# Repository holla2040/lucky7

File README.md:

Lucky7
======

7-Output Power Control Arduino Shield with sensor inputs and IR sensor<br><br>
Features<br>
1. 7 high-current (12A max) P-channel high-side MOSFETs with gate drivers. These switches have 30mOhm Rds when on. Each output has an LED indicator. 6 of the outputs are PWM controllable.<br>
2. The shield can operate up to 30VDC and supplies this voltage to the Arduino board.<br>
3. Two additional LEDs are connected to Arduino pin 8 and 13.<br>
4. 3 analog inputs: 2 for photocells, 1 for user button.<br>
5. 1 IR sensor input, such as TSOP38238.<br>
6. Input voltage sense to Arduino analog input A0.<br>
7. ATO fuse holder for wire protection in case of shorts to ground.<br>
8. Hardware design and firmware are released CC-BY-SA<br>
<br>
Fully populated and tested board is available for $20 + shipping.  Contact holla@montrosemakerspace.com for more information.
<br>
<br>
Only 10 available, order now!

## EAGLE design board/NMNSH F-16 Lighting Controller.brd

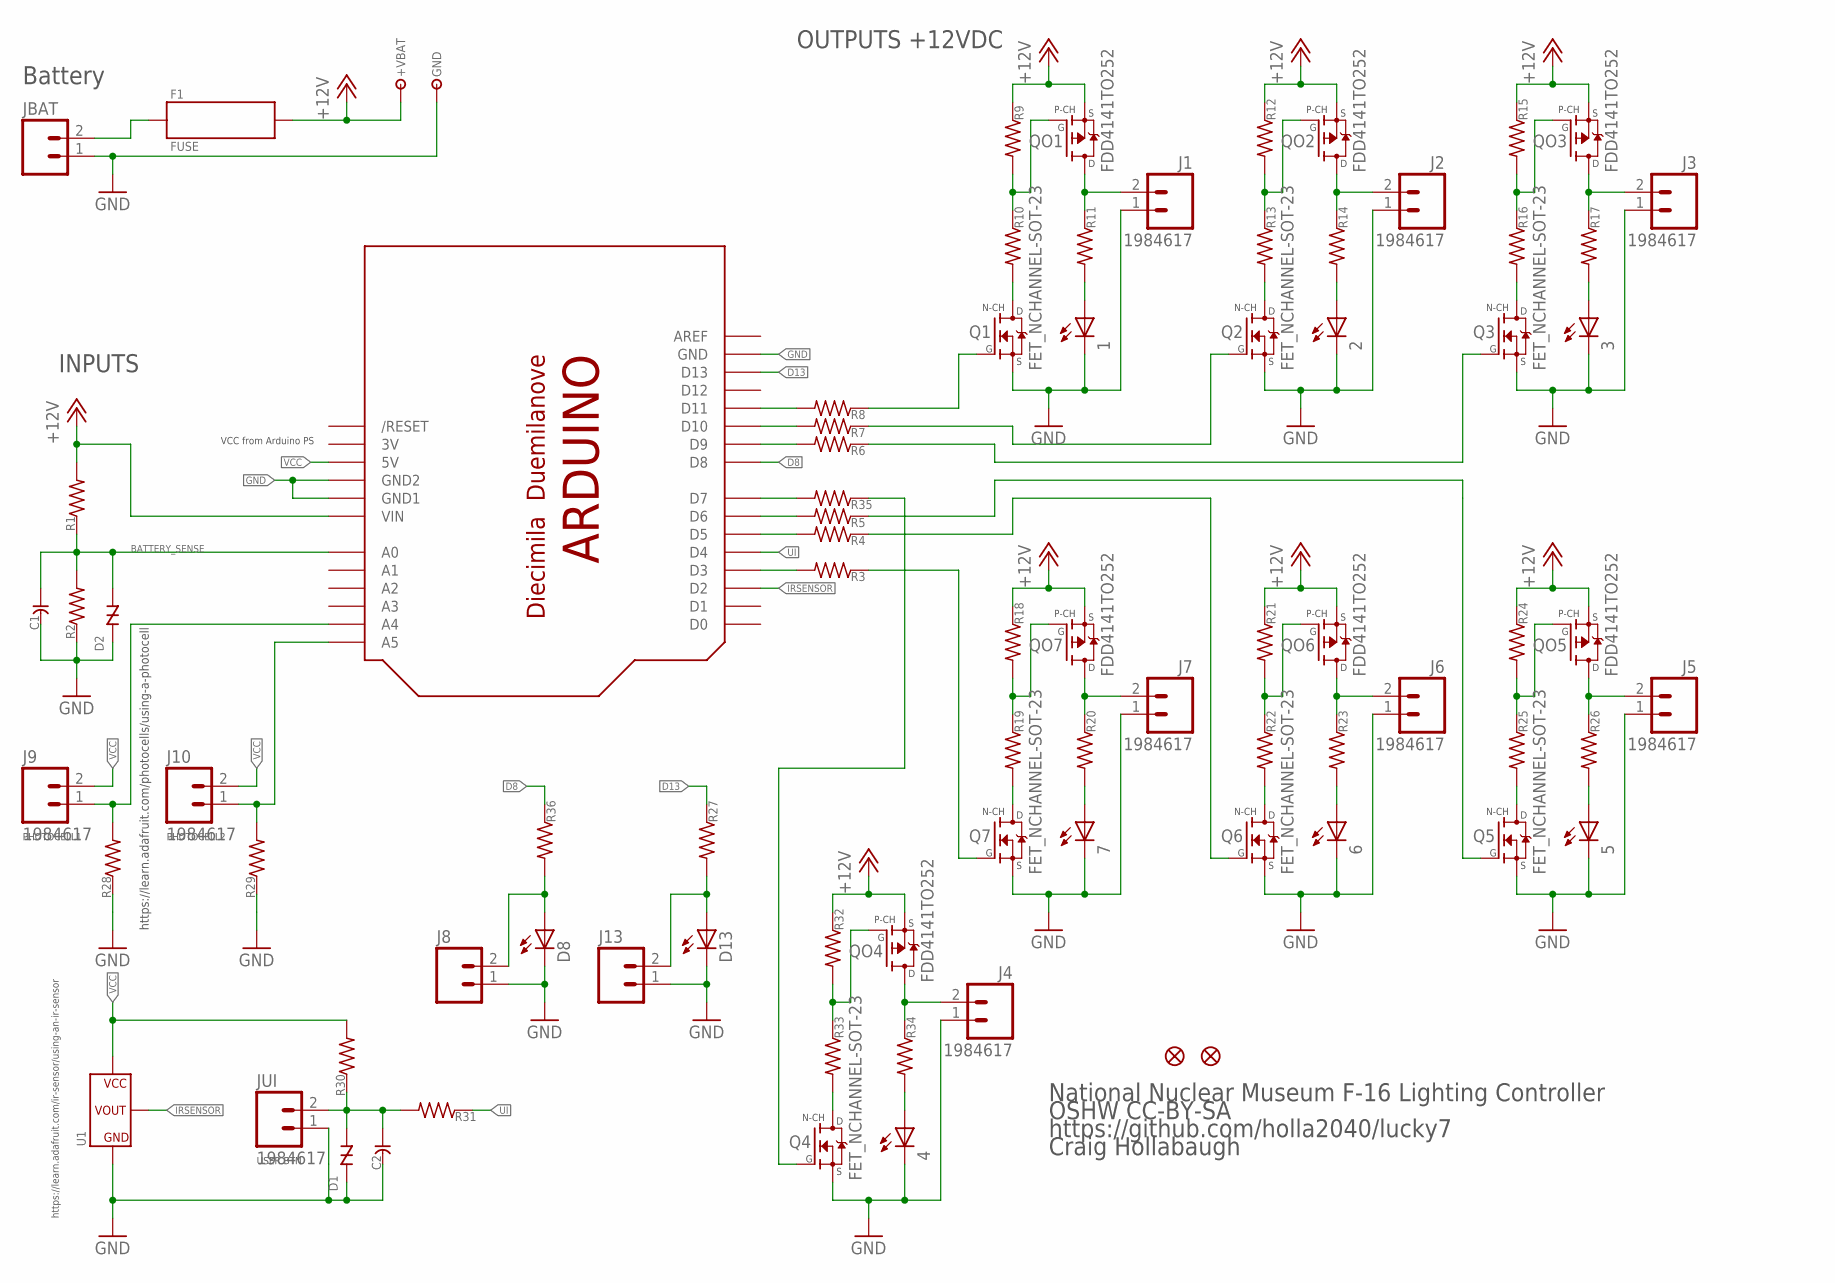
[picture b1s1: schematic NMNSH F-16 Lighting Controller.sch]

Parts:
1, 2, 3, 4, 5, 6, 7: LEDCHIP-LED0805; CHIP-LED0805
+VBAT: TESTPOINTTHRU; TPTHRU
C1, C2: C-USC0603; C0603
D1, D2: TVS0603; TVS-0603
D8, D13: LEDCHIP-LED0805; CHIP-LED0805
F1: FUSE; FUSE-3557-2
GND: TESTPOINTTHRU; TPTHRU
J1, J2, J3, J4, J5, J6, J7, J9, J10: 1984617
J8, J13: M02-0.1; 1X02
JBAT: M02-6.35MM; OSTT702
JP1, JP2: FIDUCIAL1X2; FIDUCIAL-1X2
JUI: 1984617
Q1, Q2, Q3, Q4, Q5, Q6, Q7: FET_NCHANNEL-SOT-23; SOT-23
QO1, QO2, QO3, QO4, QO5, QO6, QO7: FDD4141TO252; TO252
R1, R2, R3, R4, R5, R6, R7, R8, R9, R10, R11, R12, R13, R14, R15, R16, R17, R18, R19, R20, R21, R22, R23, R24, R25, R26, R27, R28, R29, R30, R31, R32, R33, R34, R35, R36: R-US_R0603; R0603
U1: IRDETECTOR-THRU
U100: ARDUINO-BPLACE

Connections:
3V: U100.3V
+12V: +VBAT.1, F1.2@1, F1.2@2, QO1.2 (S), QO2.2 (S), QO3.2 (S), QO4.2 (S), QO5.2 (S), QO6.2 (S), QO7.2 (S), R1.2, R9.1, R12.1, R15.1, R18.1, R21.1, R24.1, R32.1, U100.VIN
BATTERY_SENSE: C1.1, D2.1, R1.1, R2.2, U100.A0
D8: R36.1, U100.D8
D13: R27.1, U100.D13
GND: 1.C, 2.C, 3.C, 4.C, 5.C, 6.C, 7.C, C1.2, C2.2, D1.2, D2.2, D8.C, D13.C, GND.1, J1.1, J2.1, J3.1, J4.1, J5.1, J6.1, J7.1, J8.1, J13.1, JBAT.1, JUI.1, Q1.3 (S), Q2.3 (S), Q3.3 (S), Q4.3 (S), Q5.3 (S), Q6.3 (S), Q7.3 (S), R2.1, R28.1, R29.1, U1.GND, U100.GND, U100.GND1, U100.GND2
IRSENSOR: U1.VOUT, U100.D2
unnamed: QO1.1 (G), R9.2, R10.1
unnamed: Q1.1 (D), R10.2
unnamed: R8.2, U100.D11
unnamed: J9.1, R28.2, U100.A4
unnamed: 1.A, R11.2
unnamed: R7.2, U100.D10
unnamed: R6.2, U100.D9
unnamed: R5.2, U100.D6
unnamed: R4.2, U100.D5
unnamed: R3.2, U100.D3
unnamed: QO2.1 (G), R12.2, R13.1
unnamed: Q2.1 (D), R13.2
unnamed: 2.A, R14.2
unnamed: QO3.1 (G), R15.2, R16.1
unnamed: Q3.1 (D), R16.2
unnamed: 3.A, R17.2
unnamed: QO7.1 (G), R18.2, R19.1
unnamed: Q7.1 (D), R19.2
unnamed: 7.A, R20.2
unnamed: QO6.1 (G), R21.2, R22.1
unnamed: Q6.1 (D), R22.2
unnamed: 6.A, R23.2
unnamed: QO5.1 (G), R24.2, R25.1
unnamed: Q5.1 (D), R25.2
unnamed: 5.A, R26.2
unnamed: Q1.2 (G), R8.1
unnamed: Q2.2 (G), R7.1
unnamed: Q3.2 (G), R6.1
unnamed: Q5.2 (G), R5.1
unnamed: Q6.2 (G), R4.1
unnamed: Q7.2 (G), R3.1
unnamed: J10.1, R29.2, U100.A5
unnamed: C2.1, D1.1, JUI.2, R30.1, R31.2
unnamed: D13.A, J13.2, R27.2
unnamed: QO4.1 (G), R32.2, R33.1
unnamed: Q4.1 (D), R33.2
unnamed: D8.A, J8.2, R36.2
unnamed: 4.A, R34.2
unnamed: Q4.2 (G), R35.1
unnamed: R35.2, U100.D7
O1: J1.2, QO1.3 (D), R11.1
O2: J2.2, QO2.3 (D), R14.1
O3: J3.2, QO3.3 (D), R17.1
O4: J4.2, QO4.3 (D), R34.1
O5: J5.2, QO5.3 (D), R26.1
O6: J6.2, QO6.3 (D), R23.1
O7: J7.2, QO7.3 (D), R20.1
UI: R31.1, U100.D4
VBAT: F1.1@1, F1.1@2, JBAT.2
VCC: J9.2, J10.2, R30.2, U1.VCC, U100.5V

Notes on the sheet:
PHOTOCELL1
PHOTOCELL2
https://learn.adafruit.com/photocells/using-a-photocell
USER BTN
VCC from Arduino PS
https://learn.adafruit.com/ir-sensor/using-an-ir-sensor
INPUTS
OUTPUTS +12VDC
Battery
https://github.com/holla2040/lucky7
OSHW CC-BY-SA
Craig Hollabaugh
National Nuclear Museum F-16 Lighting Controller

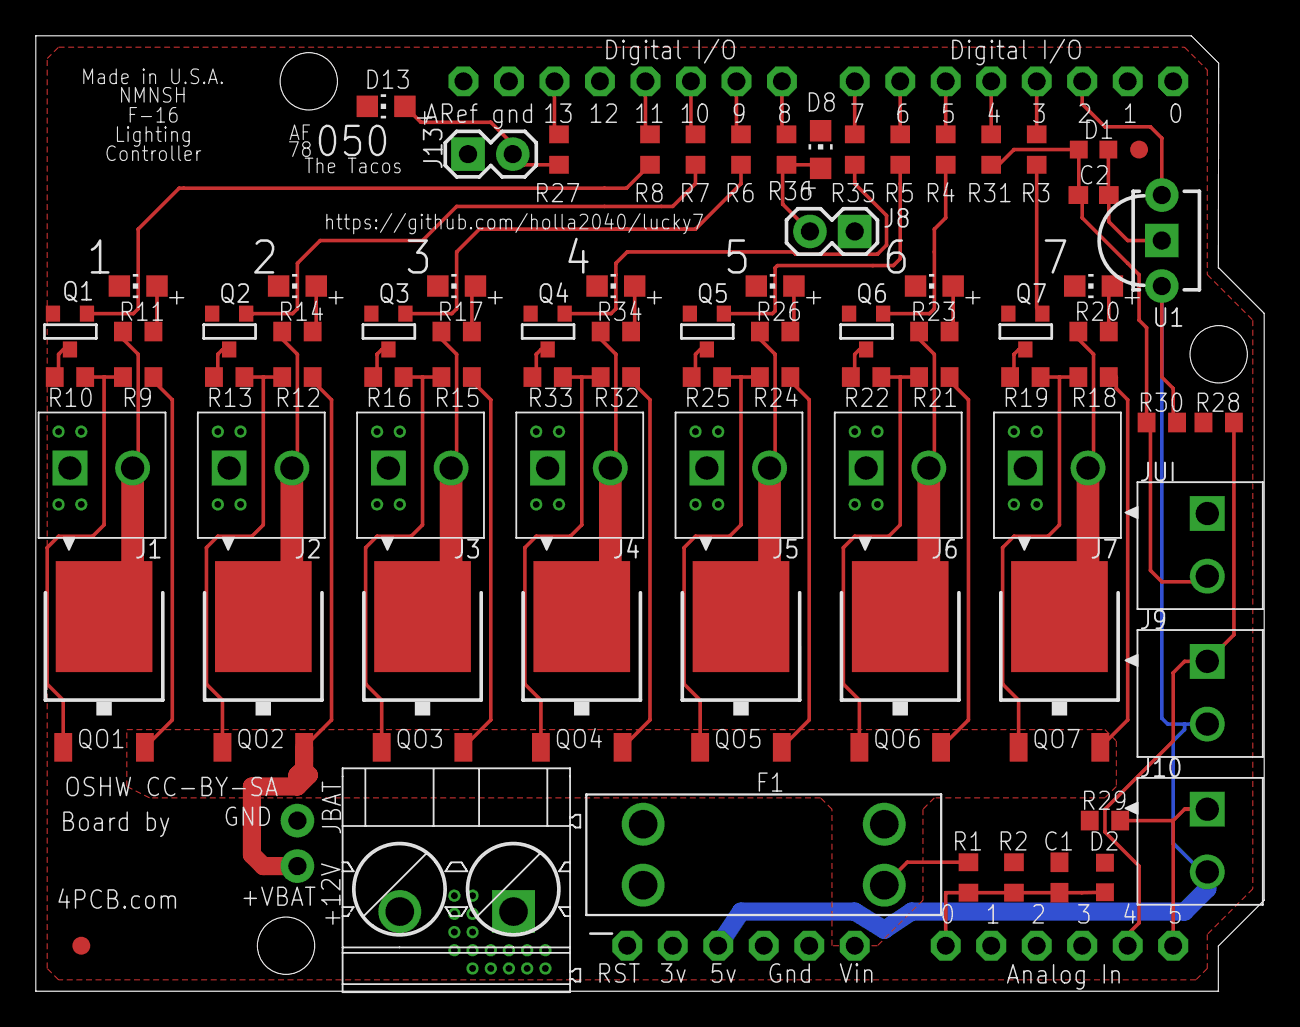
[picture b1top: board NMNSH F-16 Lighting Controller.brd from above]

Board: 2 copper layers, 68.6 x 53.3 mm, 83 parts (0 on the bottom side), 56 nets.

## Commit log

2014-09-06 initial add
2014-09-13 initial add for NMNSH variant
2014-09-13 moving these to new repo
2014-11-14 added feature list
